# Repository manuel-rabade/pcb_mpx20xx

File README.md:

PCB MPX20xx
===========

This is a PCB for the [water tank depth
sensor](http://www.practicalarduino.com/projects/water-tank-depth-sensor)
project featured in the [Practical
Arduino](http://www.practicalarduino.com) book.

From the [MPX2010
datasheet](http://www.freescale.com/files/sensors/doc/data_sheet/MPX2010.pdf):

>The MPX2010 series silicon piezoresistive pressure sensors provide a
>very accurate and linear voltage output directly proportional to the
>applied pressure. These sensors house a single monolithic silicon die
>with the strain gauge and thin film resistor network integrated. The
>sensor is laser trimmed for precise span, offset calibration and
>temperature compensation.

The MPX2010 can mesaure up to 10 kPa (in water depth equals 10 meters)
and there are other MPX20xx sensor like the
[MPX2050](http://cache.freescale.com/files/sensors/doc/data_sheet/MPX2050.pdf)
that can mesaure up to 50 kPa (about 50 meters depth).

The [mpx20xx](mpx20xx) project was done in [CadSoft
EAGLE](http://www.cadsoft.de/eagle-pcb-design-software/) 7.1.0.

Schematic
---------

PCB
---

**Artwork**

**Manufactured**

Author
------

Manuel Rábade <[manuel@rabade.net](mailto:manuel@rabade.net)>

License
-------

This work is published under a [Creative Commons Attribution 4.0
International License](http://creativecommons.org/licenses/by/4.0/).

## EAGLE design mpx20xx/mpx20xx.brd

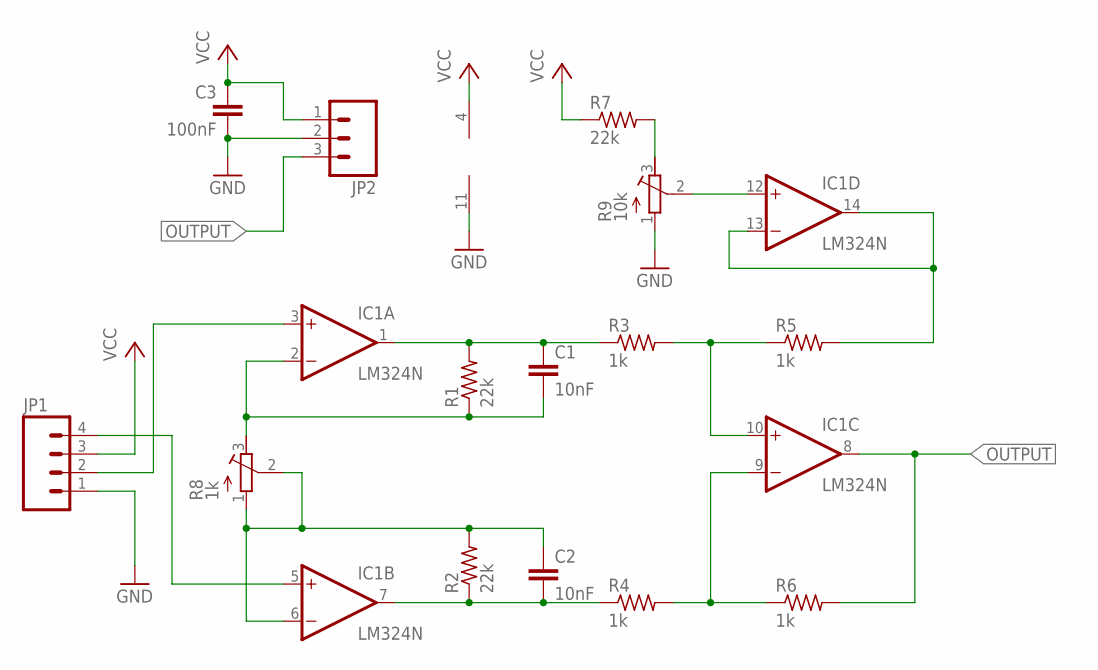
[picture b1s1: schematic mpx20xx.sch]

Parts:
C1, C2: 10nF; C050-025X075
C3: 100nF; C050-025X075
IC1: LM324N; DIL14
JP1: M04LONGPADS; 1X04_LONGPADS
JP2: M03LONGPADS; 1X03_LONGPADS
R1, R2, R7: 22k; 0207/10
R3, R4, R5, R6: 1k; 0207/10
R8: 1k; RTRIM3299W
R9: 10k; RTRIM3299W

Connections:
GND: C3.2, IC1.11 (V-), JP1.1, JP2.2, R9.1 (A)
unnamed: IC1.3 (+IN), JP1.2
unnamed: IC1.5 (+IN), JP1.4
unnamed: C1.1, IC1.1 (OUT), R1.2, R3.1
unnamed: IC1.10 (+IN), R3.2, R5.1
unnamed: C1.2, IC1.2 (-IN), R1.1, R8.3 (E)
unnamed: C2.2, IC1.7 (OUT), R2.1, R4.1
unnamed: IC1.9 (-IN), R4.2, R6.1
unnamed: C2.1, IC1.6 (-IN), R2.2, R8.1 (A), R8.2 (S)
unnamed: IC1.13 (-IN), IC1.14 (OUT), R5.2
unnamed: IC1.12 (+IN), R9.2 (S)
unnamed: R7.2, R9.3 (E)
OUTPUT: IC1.8 (OUT), JP2.3, R6.2
VCC: C3.1, IC1.4 (V+), JP1.3, JP2.1, R7.1

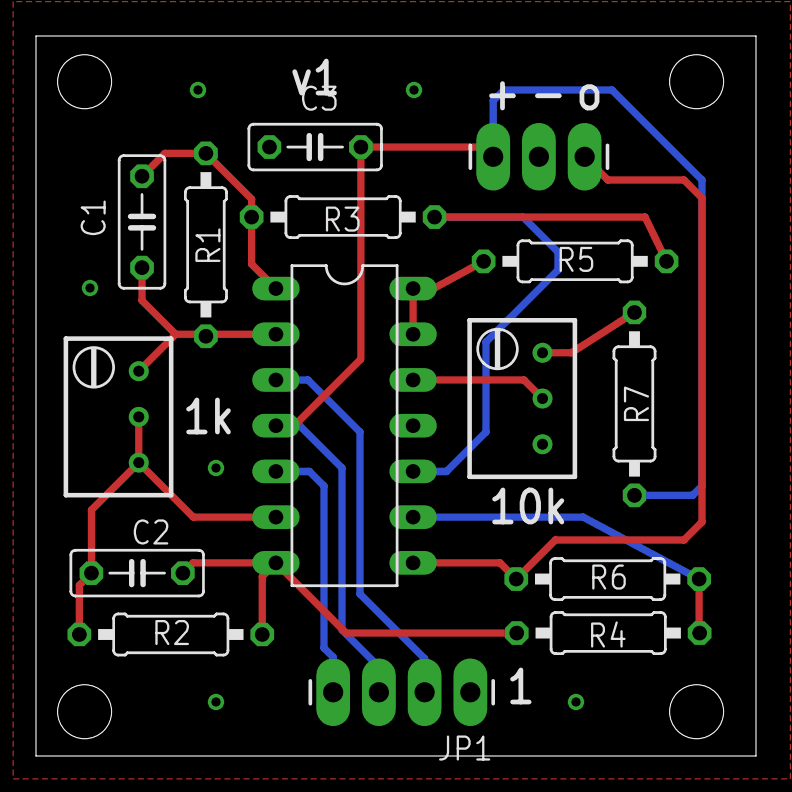
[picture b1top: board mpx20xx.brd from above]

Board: 2 copper layers, 40.0 x 40.0 mm, 15 parts (0 on the bottom side), 14 nets.

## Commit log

2014-10-14 importando proyecto de eagle
2014-10-15 draft readme
2014-10-15 estilo readme
2014-10-15 typo readme
2014-11-18 foto pcb
2014-11-20 imagen pcb
2015-01-27 misc license

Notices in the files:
parts and their libraries:
SparkFun-Connectors: Licensing: CC v3.0 Share-Alike You are welcome to use this library for commercial purposes.
